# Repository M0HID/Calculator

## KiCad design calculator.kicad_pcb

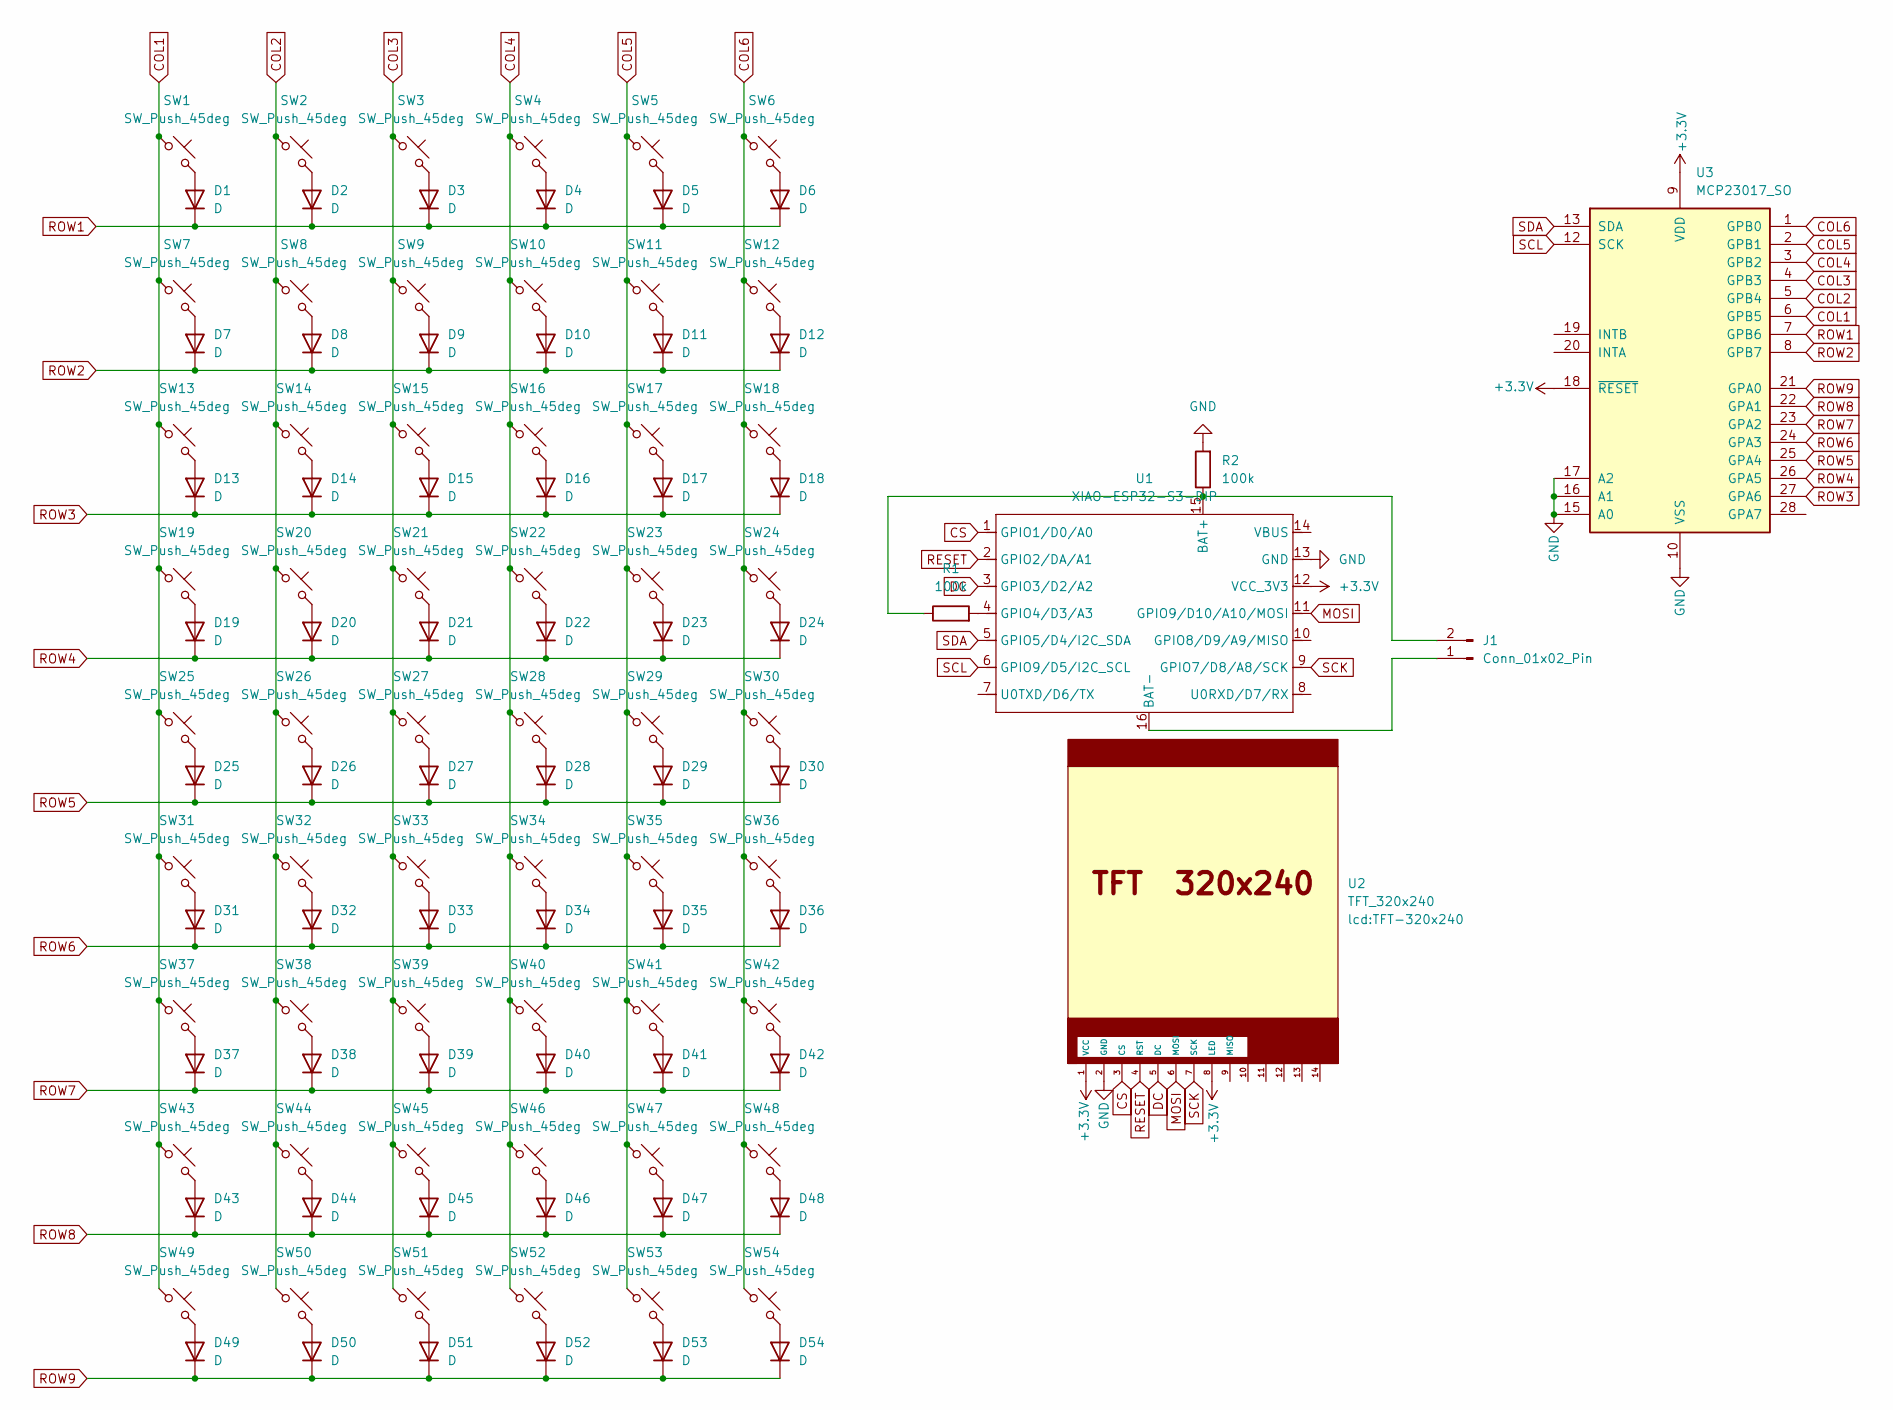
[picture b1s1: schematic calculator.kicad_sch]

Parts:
D1, D2, D3, D4, D5, D6, D7, D8, D9, D10, D11, D12, D13, D14, D15, D16, D17, D18, D19, D20, D21, D22, D23, D24, D25, D26, D27, D28, D29, D30, D31, D32, D33, D34, D35, D36, D37, D38, D39, D40, D41, D42, D43, D44, D45, D46, D47, D48, D49, D50, D51, D52, D53, D54: D; D_SOD-123
J1: Conn_01x02_Pin; PinHeader_1x02_P2.54mm_Vertical
R1, R2: 100k; R_0402_1005Metric_Pad0.72x0.64mm_HandSolder
SW1, SW2, SW3, SW4, SW5, SW6, SW7, SW8, SW9, SW10, SW11, SW12, SW13, SW14, SW15, SW16, SW17, SW18, SW19, SW20, SW21, SW22, SW23, SW24, SW25, SW26, SW27, SW28, SW29, SW30, SW31, SW32, SW33, SW34, SW35, SW36, SW37, SW38, SW39, SW40, SW41, SW42, SW43, SW44, SW45, SW46, SW47, SW48, SW49, SW50, SW51, SW52, SW53, SW54: SW_Push_45deg; 2pinsilent
U1: XIAO-ESP32-S3-DIP; XIAO-ESP32S3-SMD
U2: TFT_320x240; TFT-320x240
U3: MCP23017_SO; SOIC-28W_7.5x17.9mm_P1.27mm

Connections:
+3.3V: U1.12 (VCC_3V3), U2.1 (VCC), U2.8 (LED), U3.9 (VDD), U3.18 (~RESET)
COL1: SW1.1, SW7.1, SW13.1, SW19.1, SW25.1, SW31.1, SW37.1, SW43.1, SW49.1, U3.6 (GPB5)
COL2: SW2.1, SW8.1, SW14.1, SW20.1, SW26.1, SW32.1, SW38.1, SW44.1, SW50.1, U3.5 (GPB4)
COL3: SW3.1, SW9.1, SW15.1, SW21.1, SW27.1, SW33.1, SW39.1, SW45.1, SW51.1, U3.4 (GPB3)
COL4: SW4.1, SW10.1, SW16.1, SW22.1, SW28.1, SW34.1, SW40.1, SW46.1, SW52.1, U3.3 (GPB2)
COL5: SW5.1, SW11.1, SW17.1, SW23.1, SW29.1, SW35.1, SW41.1, SW47.1, SW53.1, U3.2 (GPB1)
COL6: SW6.1, SW12.1, SW18.1, SW24.1, SW30.1, SW36.1, SW42.1, SW48.1, SW54.1, U3.1 (GPB0)
CS: U1.1 (GPIO1/D0/A0), U2.3 (CS)
DC: U1.3 (GPIO3/D2/A2), U2.5 (DC)
GND: R2.2, U1.13 (GND), U2.2 (GND), U3.10 (VSS), U3.15 (A0), U3.16 (A1), U3.17 (A2)
MOSI: U1.11 (GPIO9/D10/A10/MOSI), U2.6 (MOSI)
unnamed: D1.2 (A), SW1.2
unnamed: D2.2 (A), SW2.2
unnamed: D3.2 (A), SW3.2
unnamed: D4.2 (A), SW4.2
unnamed: D5.2 (A), SW5.2
unnamed: D6.2 (A), SW6.2
unnamed: D7.2 (A), SW7.2
unnamed: D8.2 (A), SW8.2
unnamed: D9.2 (A), SW9.2
unnamed: D10.2 (A), SW10.2
unnamed: D11.2 (A), SW11.2
unnamed: D12.2 (A), SW12.2
unnamed: D13.2 (A), SW13.2
unnamed: D14.2 (A), SW14.2
unnamed: D15.2 (A), SW15.2
unnamed: D16.2 (A), SW16.2
unnamed: D17.2 (A), SW17.2
unnamed: D18.2 (A), SW18.2
unnamed: D19.2 (A), SW19.2
unnamed: D20.2 (A), SW20.2
unnamed: D21.2 (A), SW21.2
unnamed: D22.2 (A), SW22.2
unnamed: D23.2 (A), SW23.2
unnamed: D24.2 (A), SW24.2
unnamed: D25.2 (A), SW25.2
unnamed: D26.2 (A), SW26.2
unnamed: D27.2 (A), SW27.2
unnamed: D28.2 (A), SW28.2
unnamed: D29.2 (A), SW29.2
unnamed: D30.2 (A), SW30.2
unnamed: D31.2 (A), SW31.2
unnamed: D32.2 (A), SW32.2
unnamed: D33.2 (A), SW33.2
unnamed: D34.2 (A), SW34.2
unnamed: D35.2 (A), SW35.2
unnamed: D36.2 (A), SW36.2
unnamed: D37.2 (A), SW37.2
unnamed: D38.2 (A), SW38.2
unnamed: D39.2 (A), SW39.2
unnamed: D40.2 (A), SW40.2
unnamed: D41.2 (A), SW41.2
unnamed: D42.2 (A), SW42.2
unnamed: D43.2 (A), SW43.2
unnamed: D44.2 (A), SW44.2
unnamed: D45.2 (A), SW45.2
unnamed: D46.2 (A), SW46.2
unnamed: D47.2 (A), SW47.2
unnamed: D48.2 (A), SW48.2
unnamed: D49.2 (A), SW49.2
unnamed: D50.2 (A), SW50.2
unnamed: D51.2 (A), SW51.2
unnamed: D52.2 (A), SW52.2
unnamed: D53.2 (A), SW53.2
unnamed: D54.2 (A), SW54.2
unnamed: J1.1, U1.16 (BAT-)
unnamed: J1.2, R1.1, R2.1, U1.15 (BAT+)
unnamed: R1.2, U1.4 (GPIO4/D3/A3)
RESET: U1.2 (GPIO2/DA/A1), U2.4 (RST)
ROW1: D1.1 (K), D2.1 (K), D3.1 (K), D4.1 (K), D5.1 (K), D6.1 (K), U3.7 (GPB6)
ROW2: D7.1 (K), D8.1 (K), D9.1 (K), D10.1 (K), D11.1 (K), D12.1 (K), U3.8 (GPB7)
ROW3: D13.1 (K), D14.1 (K), D15.1 (K), D16.1 (K), D17.1 (K), D18.1 (K), U3.27 (GPA6)
ROW4: D19.1 (K), D20.1 (K), D21.1 (K), D22.1 (K), D23.1 (K), D24.1 (K), U3.26 (GPA5)
ROW5: D25.1 (K), D26.1 (K), D27.1 (K), D28.1 (K), D29.1 (K), D30.1 (K), U3.25 (GPA4)
ROW6: D31.1 (K), D32.1 (K), D33.1 (K), D34.1 (K), D35.1 (K), D36.1 (K), U3.24 (GPA3)
ROW7: D37.1 (K), D38.1 (K), D39.1 (K), D40.1 (K), D41.1 (K), D42.1 (K), U3.23 (GPA2)
ROW8: D43.1 (K), D44.1 (K), D45.1 (K), D46.1 (K), D47.1 (K), D48.1 (K), U3.22 (GPA1)
ROW9: D49.1 (K), D50.1 (K), D51.1 (K), D52.1 (K), D53.1 (K), D54.1 (K), U3.21 (GPA0)
SCK: U1.9 (GPIO7/D8/A8/SCK), U2.7 (SCK)
SCL: U1.6 (GPIO9/D5/I2C_SCL), U3.12 (SCK)
SDA: U1.5 (GPIO5/D4/I2C_SDA), U3.13 (SDA)

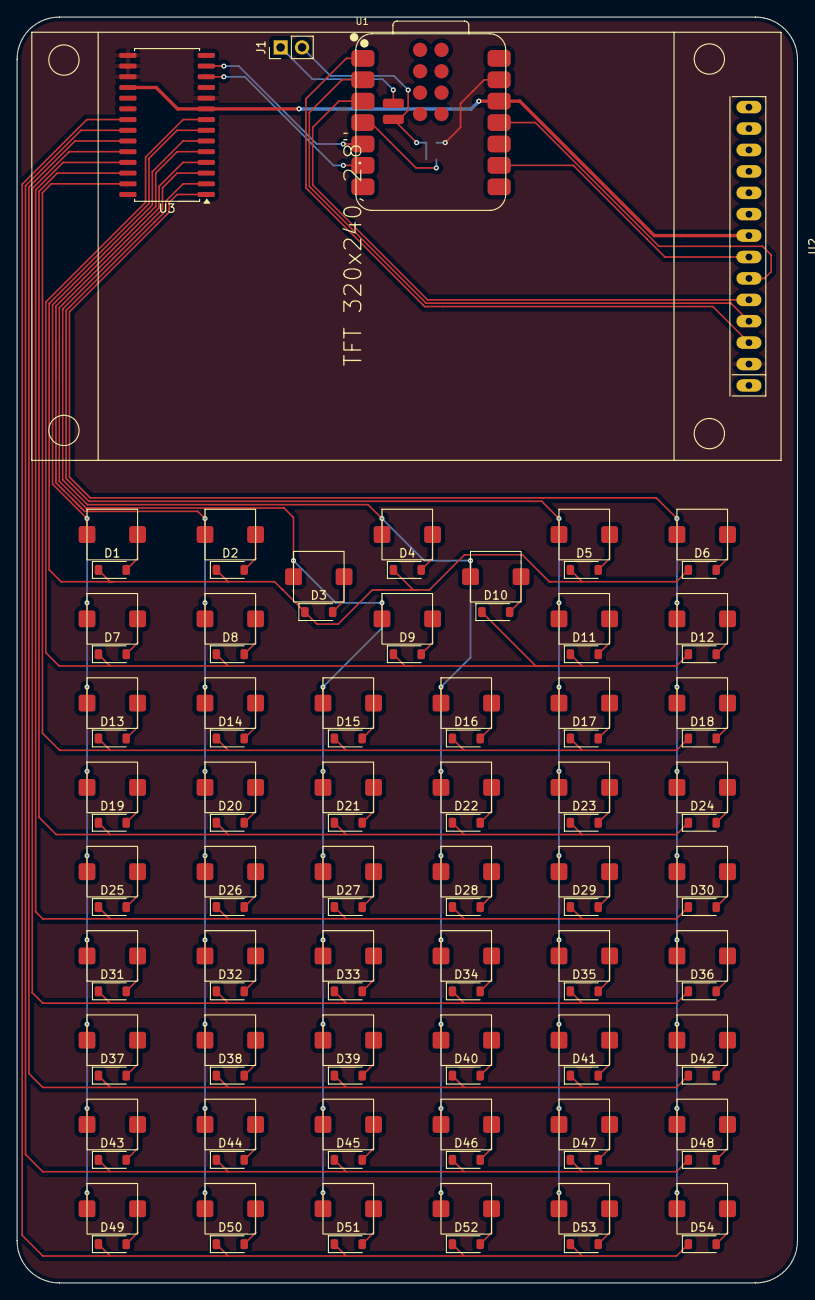
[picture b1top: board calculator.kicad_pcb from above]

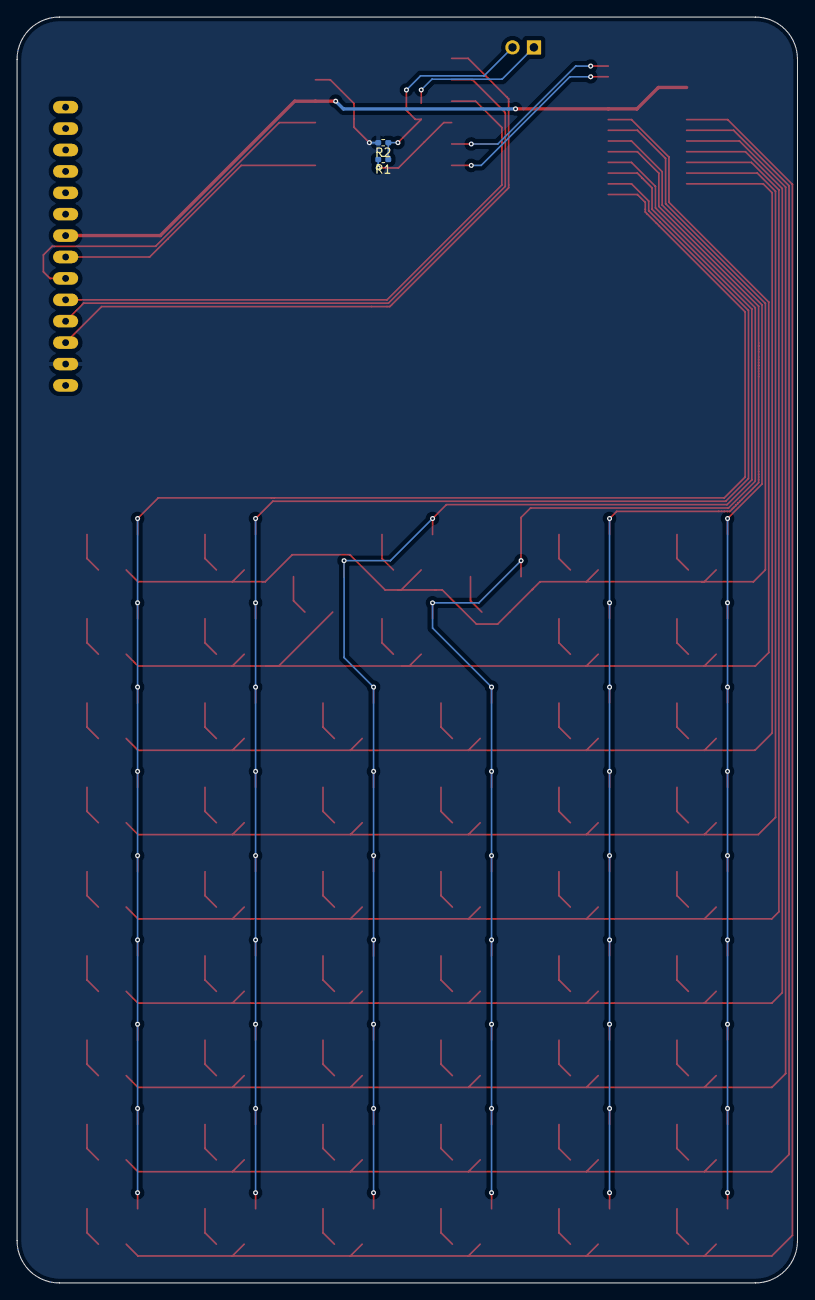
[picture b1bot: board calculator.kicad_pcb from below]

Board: 2 copper layers, 92.6 x 150.2 mm, 114 parts (2 on the bottom side), 81 nets.

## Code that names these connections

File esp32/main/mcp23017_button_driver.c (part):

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#define MCP23017_I2C_ADDR           0x20    // Default I2C address

// Matrix configuration based on your wiring:
// Port B (GPIOB): GPB0-GPB5 = COL6-COL1, GPB6-GPB7 = ROW1-ROW2
// Port A (GPIOA): GPA0-GPA6 = ROW9-ROW3
#define MATRIX_ROWS 9
#define MATRIX_COLS 6

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
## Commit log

2026-02-04 Fix button keycode loading - copy config file to bin directory and add fallback paths
2026-02-04 Remove windows submodule
2026-02-04 Rename windows to desktop, add .gitignore, remove build artifacts
2026-02-04 add graph
2026-02-04 Graph app: multi-function UI, Casio-inspired UX, ESP32 keybindings
    - Add function list screen with y1-y4 equations
    - Add graph view with pan/zoom/trace
    - Support multiple functions with different colors
    - Light theme UI (white backgrounds)
    - ESP32 keyboard bindings:
    - CALC: go to graph view
2026-02-09 Add solver, stats, and mechanics apps with reusable submenu UI system
    Major additions:
    - Solver app: Linear, quadratic, and Newton-Raphson equation solvers with menu-based navigation
    - Stats app: Binomial and normal distribution calculators (PMF, CDF, inverse normal) with individual screens per distribution
    - Mechanics app: SUVAT equation solver for kinematics problems
    - Reusable submenu UI component (ui_submenu.c/h) for consistent vertical list menus across apps
    - Custom math fonts (font_math_12.c/14.c) with Greek letters and mathematical symbols for proper rendering
2026-02-10 modified: design.md modified: desktop/CMakeLists.txt modified: esp32/main/CMakeLists.txt modified: src/button_keymap.c modified: src/expr_eval.c modified: src/graph.c modified: src/main_menu.c delete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
2026-03-01 Add numerical methods app and update techsolution v2 documentation with arguments, purpose, and objectives per function
2026-03-04 Add HCI and evaluation docs, fix pi rendering on keypad, update source files
2026-03-04 Expand file purpose descriptions in techsolution v2
2026-03-04 Add problems, lessons learned sections to evaluation
2026-03-05 Add iteration log table to evaluation
2026-03-05 Reformat iteration log to match required style
